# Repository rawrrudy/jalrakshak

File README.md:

<h1 align="center"> JalRakshak </h1>

<p align="center">
  Water Monitoring Device
</p>

<p align="center">
  An ESP-32 powered "floating" water monitoring device with pH, Temperature, TDS and Turbidity sensors!
</p>

# Index

#### [1) JalRakshak Zine](#jalrakshak-zine)
#### [2) What is JalRakshak?](#what-is-jalrakshak)
#### [3) Why was JalRakshak made?](#why-was-jalrakshak-made)
#### [4) Key Features](#key-features)
#### [5) PCB](#pcb)
#### [6) Images](#images)
#### [7) How to Build and Run?](#how-to-build-and-run)
#### [8) Credits](#credits)
#### [9) License](#license)

# JalRakshak Zine

# What is JalRakshak?

JalRakshak is an ESP32 powered water quality monitoring device, that continously measures pH, TDS, Turbidity, Temperature and Water Level! It uses a custom built PCB and enclosure to help communities protect lakes, reservoirs and local water bodies.

<p align="center">
 A basic 3D outline of JalRakshak V1
</p>

# Why was JalRakshak made?

Water pollution is one of the biggest challenges to the environment in recent days. Not only does it affect aquatic fauna, it can also cause significant damage to humans due to unhygenic conditions of water. This issue is widespread in rural areas, especially in the country I am from, India. To help combat this issue, even at a significantly smaller scale, JalRakshak was created. Attached is a link to a credible source which discusses the major problems caused due to water pollution - 

https://www.frontiersin.org/journals/environmental-science/articles/10.3389/fenvs.2022.880246/full

# Key Features

- ESP32 microcontroller with integrated Wi-Fi
- Analyses Temperature, TDS, Turbidity, pH and Water Level
- Sends an alert via email when safety threshold is exceeded
- Custom designed PCB for sensor integration
- DS18B20 waterproof temperature sensor
- DFRobot Gravity pH and TDS sensor
- SEN0189 turbidity sensing for water clarity check
- HC-SR04 ultrasonic water level measurement
- Custom CAD optimised to float on water

# PCB

<p align="center">
  Fig. 1) Top view of the PCB layout for JalRakshak
</p>

<p align="center">
  Fig. 2) Manufacturing layout of the PCB design
</p>

<p align="center">
  Fig. 3) Schematic design of JalRakshak
</p>

# Images

<details>
<summary><b> 3D Model</b></summary>

<br>

<p align="center">
  
  <br>
  <em>Fully assembled JalRakshak enclosure.</em>
</p>

<br>

<p align="center">
  
  <br>
  <em>Exploded view showing internal components.</em>
</p>

<br>

<p align="center">
  
  <br>
  <em>Deployed image of a JalRakshak model.</em>
</p>
</details>

<details>
<summary><b> Dashboard </b></summary>

<br>

<p align="center">
  
  <br>
  <em>Sign Up/Login page of JalRakshak.</em>
</p>

<br>

<p align="center">
  
  <br>
  <em>Frontend dashboard of JalRakshak website.</em>
</p>
</details>

<details>
<summary><b>3D PCB Visuals</b></summary>

<br>

<p align="center">

  <br>
  <em>Visuals of 3D version of PCB.</em>
</p>
</details>

<details>
<summary><b> Other essentials </b></summary>

<br>

<p align="center">
  
  <br>
  <em>Fully labelled visual of JalRakshak.</em>
</p>

<p align="center">
  
  <br>
  <em>Visuals of all the probes of JalRakshak.</em>
</p>

<p align="center">
  
  <br>
  <em>Demo prototype of screen of JalRakshak.</em>
</p>
</details>

# How to Build and Run?

>⚠️ Note: At the time of writing, JalRakshak is in the prototype development stage. The assembly and deployment instructions below describe the intended hardware workflow based on the completed PCB, CAD enclosure and firmware design.

Please check the [BOM](BOM.csv) before building this project!

<details>
<summary><b> Hardware </b></summary>

<br>

1. Fabricate or order the JalRakshak PCB using the provided [Gerber](hardware/gerbers) files.
2. Solder the ESP32 and supporting components onto the PCB.
3. Connect the sensors to their designated headers:
   - pH Sensor
   - TDS Sensor
   - Turbidity Sensor
   - DS18B20 Temperature Sensor
   - HC-SR04 Ultrasonic Sensor
4. Mount the PCB inside the enclosure.
5. Route the sensor cables through the enclosure openings.
6. Secure all components and close the enclosure.

</details>

<details>
<summary><b> Firmware Installation </b></summary>

<br>

1. Open the Arduino IDE.
2. Install ESP32 board support through the Board Manager.
3. Install the required libraries:
   - OneWire
   - DallasTemperature
4. Open firmware/jalrakshak_main.ino
5. Upload the firmware to the ESP32.

</details>

<details>
<summary><b> Wiring </b></summary>

<br>

Connect all sensors to the custom JalRakshak PCB according to the schematic available in the repository.

| Component | Connection Type |
|------------|----------------|
| pH Sensor | Analog Input |
| TDS Sensor | Analog Input |
| Turbidity Sensor | Analog Input |
| DS18B20 Temperature Sensor | Digital GPIO |
| HC-SR04 Ultrasonic Sensor | Trigger/Echo GPIO |
| ESP32 | Main Controller |

Refer to the PCB schematic and wiring diagram in the `hardware/pcb` directory for detailed pin mappings.

</details>

<details>
<summary><b> Backend Setup </b></summary>

1. Navigate to the backend directory.
```bash
cd backend
```
2. Create and activate a Python virtual environment.
```bash
python -m venv venv
```
3. Install dependencies.
```bash
pip install -r requirements.txt
```
4. Configure PostgreSQL credentials.
5. Start the FastAPI server.
```bash
uvicorn app.main:app --reload
```

</details>

<details>
<summary><b> Dashboard setup </b></summary>

<br>

1. Navigate to the frontend directory.
```bash
cd frontend
```
2. Install dependencies.
```bash
npm install
```
3. Start the development server.
```bash
npm run dev
```
6. Open the URL displayed in the terminal.
7. Ensure the backend server is running and connected to the database.
8. Verify that live sensor readings are visible on the dashboard.

</details>

<details>
<summary><b> Operation </b></summary>

<br>

1. Power on the device.
2. Place JalRakshak on the water surface.
3. Ensure all sensors are submerged properly.
4. Open the Serial Monitor at 115200 baud.
5. Observe live readings for:
   - pH
   - TDS
   - Temperature
   - Turbidity
   - Water Level
6. Voila! Your very own version of JalRakshak is prepared!
</details>

# Credits

I would like to thank-

[KiCad](https://www.kicad.org/)

[Arduino](https://www.arduino.cc/)

[HackClub Fallout](https://fallout.hackclub.com/)

[SketchUp](https://www.sketchup.com/)

[PostgresSQL](https://www.postgresql.org/)

# License 

This project is licensed under the MIT License. See the [LICENSE](LICENSE) file for more details.

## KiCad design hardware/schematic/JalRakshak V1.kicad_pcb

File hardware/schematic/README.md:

# JalRakshak Schematic

This folder contains the KiCad schematic files for JalRakshak.

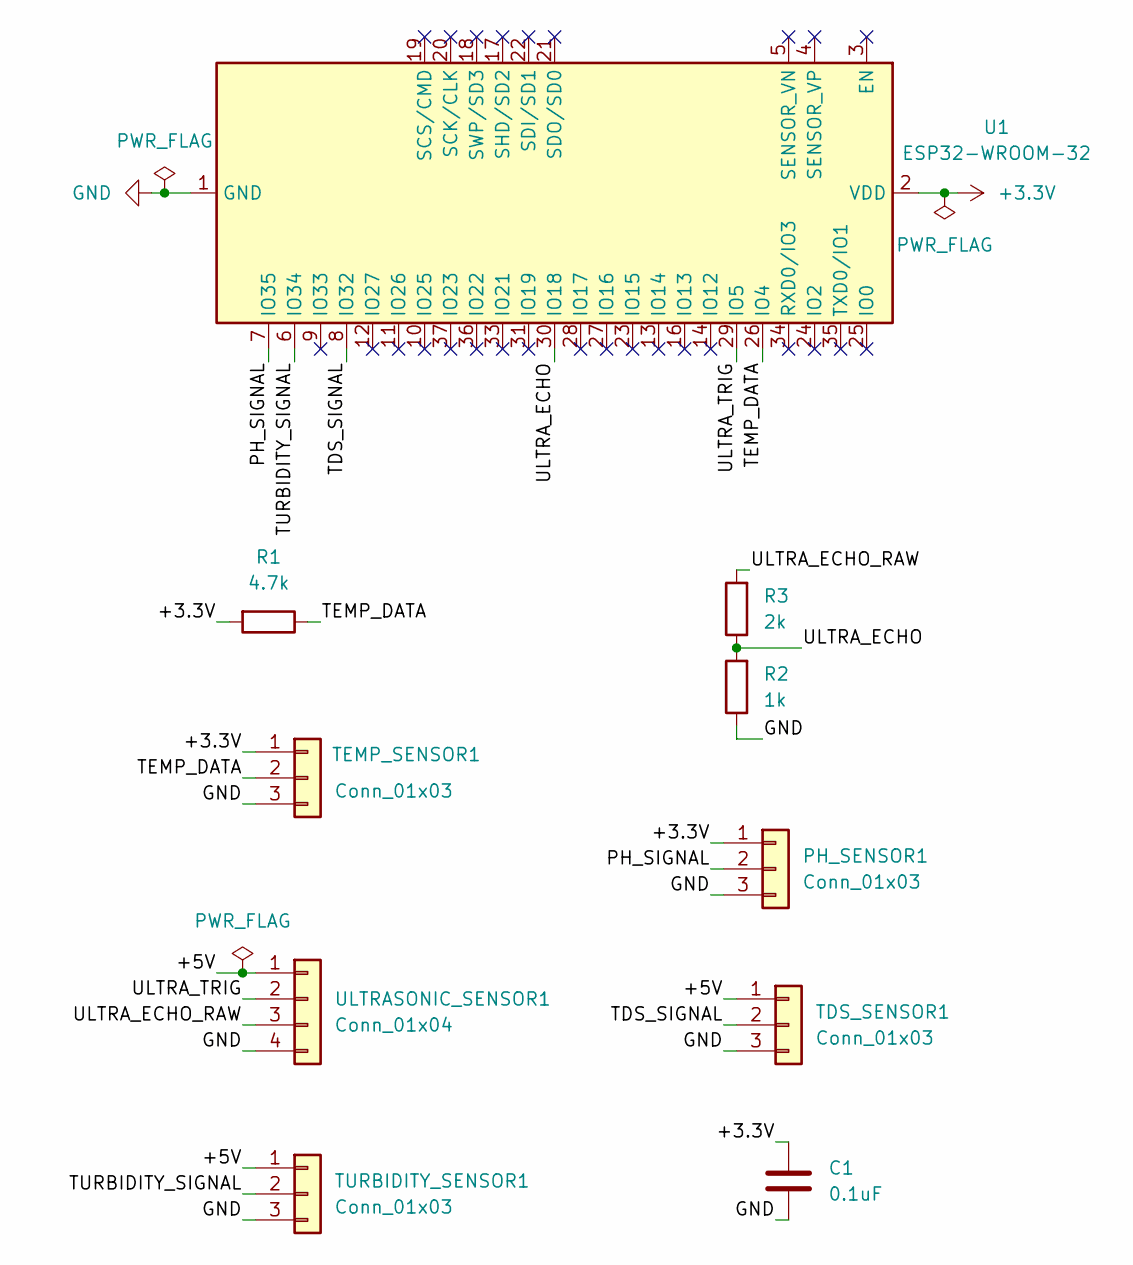
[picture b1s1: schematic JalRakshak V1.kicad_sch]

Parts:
C1: 0.1uF; C_Disc_D5.0mm_W2.5mm_P5.00mm
PH_SENSOR1: Conn_01x03; PinHeader_1x03_P2.54mm_Vertical
R1: 4.7k; R_Axial_DIN0207_L6.3mm_D2.5mm_P7.62mm_Horizontal
R2: 1k; R_Axial_DIN0207_L6.3mm_D2.5mm_P7.62mm_Horizontal
R3: 2k; R_Axial_DIN0207_L6.3mm_D2.5mm_P7.62mm_Horizontal
TDS_SENSOR1: Conn_01x03; PinHeader_1x03_P2.54mm_Vertical
TEMP_SENSOR1: Conn_01x03; PinHeader_1x03_P2.54mm_Vertical
TURBIDITY_SENSOR1: Conn_01x03; PinHeader_1x03_P2.54mm_Vertical
U1: ESP32-WROOM-32
ULTRASONIC_SENSOR1: Conn_01x04; PinHeader_1x04_P2.54mm_Vertical

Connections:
+3.3V: C1.1, PH_SENSOR1.1, R1.2, TEMP_SENSOR1.1, U1.2 (VDD)
/+5V: TDS_SENSOR1.1, TURBIDITY_SENSOR1.1, ULTRASONIC_SENSOR1.1
/PH_SIGNAL: PH_SENSOR1.2, U1.7 (IO35)
/TDS_SIGNAL: TDS_SENSOR1.2, U1.8 (IO32)
/TEMP_DATA: R1.1, TEMP_SENSOR1.2, U1.26 (IO4)
/TURBIDITY_SIGNAL: TURBIDITY_SENSOR1.2, U1.6 (IO34)
/ULTRA_ECHO: R2.2, R3.1, U1.30 (IO18)
/ULTRA_ECHO_RAW: R3.2, ULTRASONIC_SENSOR1.3
/ULTRA_TRIG: U1.29 (IO5), ULTRASONIC_SENSOR1.2
GND: C1.2, PH_SENSOR1.3, R2.1, TDS_SENSOR1.3, TEMP_SENSOR1.3, TURBIDITY_SENSOR1.3, U1.1 (GND), U1.15 (GND), U1.38 (GND), U1.39 (GND), ULTRASONIC_SENSOR1.4

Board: 2 copper layers, 10 parts (0 on the bottom side), 10 nets, no tracks yet.

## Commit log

2026-05-30 Create .gitkeep backend
2026-05-30 Create .gitkeep hardware
2026-05-30 Create .gitkeep docs
2026-05-30 Create .gitkeep schematic
2026-05-30 Create .gitkeep pcb
2026-05-30 Create .gitkeep firmware
2026-05-30 Create .gitkeep ss
2026-05-30 Create .gitkeep arch.
2026-06-01 Create project
2026-06-03 Add frontend backend and hardware files
2026-06-20 feat: add analytics dashboard and interactive monitoring map
